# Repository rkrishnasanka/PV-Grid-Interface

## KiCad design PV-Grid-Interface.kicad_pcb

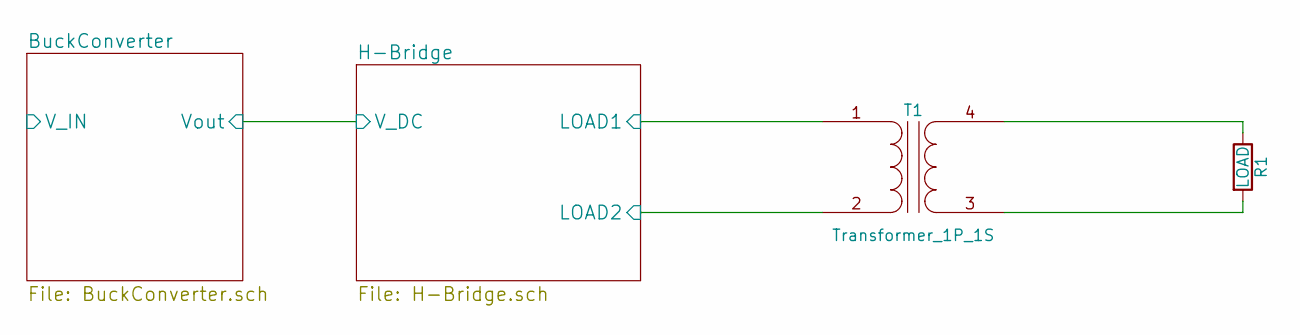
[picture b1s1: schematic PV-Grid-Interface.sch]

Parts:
R1: LOAD
T1: Transformer_1P_1S

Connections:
unnamed: R1.1, T1.4 (SB)
unnamed: R1.2, T1.3 (SA)

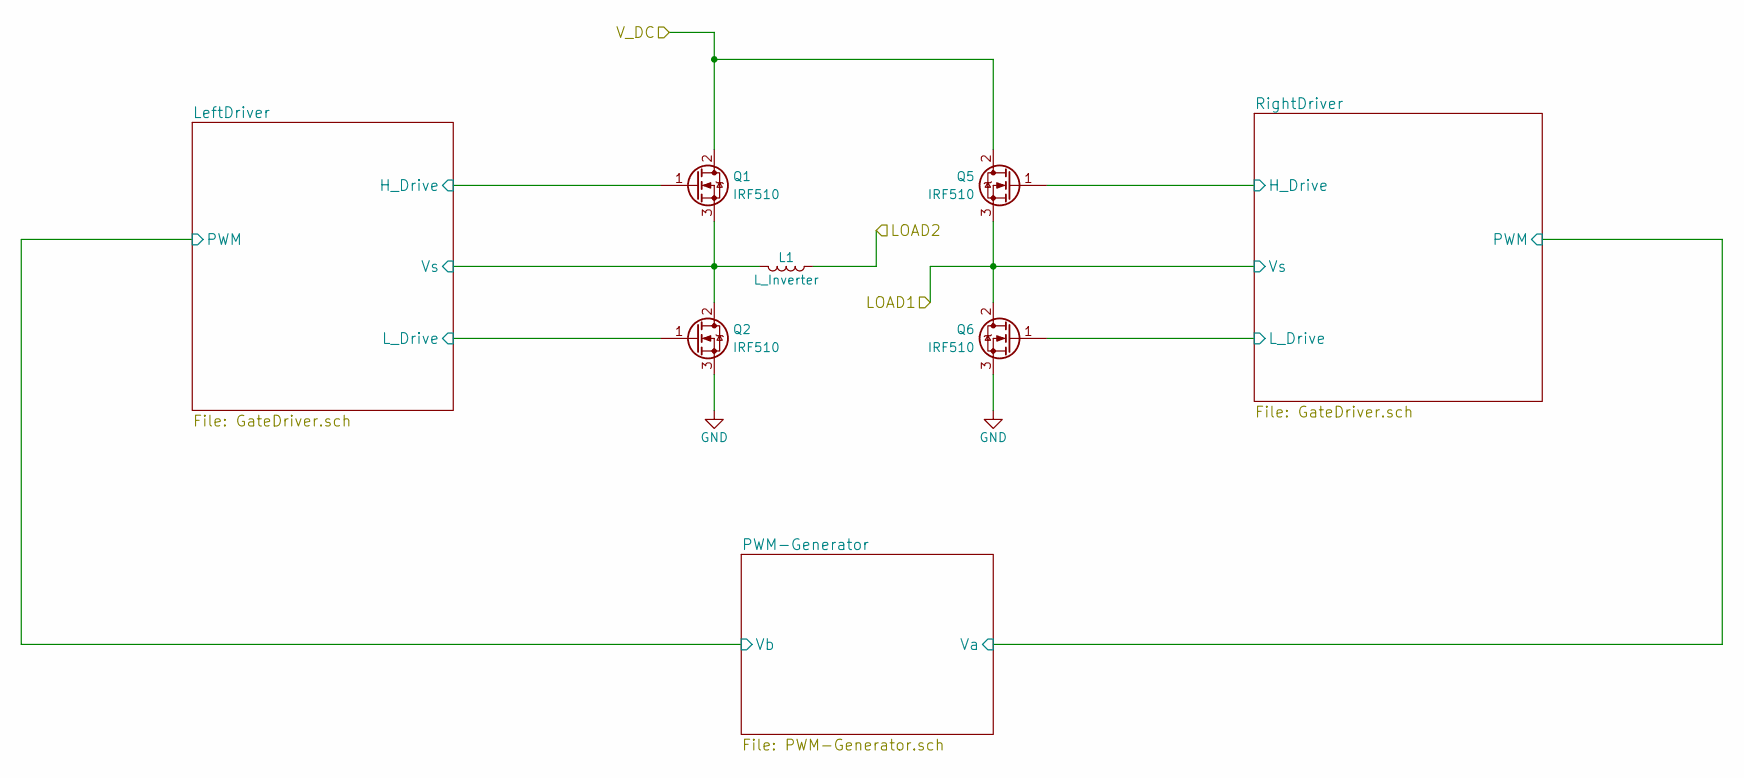
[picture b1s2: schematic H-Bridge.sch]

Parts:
L1: L_Inverter
Q1, Q2, Q5, Q6: IRF510; TO-220_Neutral123_Vertical

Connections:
/H-Bridge/LOAD1: Q5.3 (S), Q6.2 (D); also elsewhere on the board
/H-Bridge/LeftDriver/H_Drive: Q1.1 (G); also elsewhere on the board
/H-Bridge/LeftDriver/L_Drive: Q2.1 (G); also elsewhere on the board
/H-Bridge/LeftDriver/Vs: L1.2, Q1.3 (S), Q2.2 (D); also elsewhere on the board
/H-Bridge/RightDriver/H_Drive: Q5.1 (G); also elsewhere on the board
/H-Bridge/RightDriver/L_Drive: Q6.1 (G); also elsewhere on the board
/H-Bridge/V_DC: Q1.2 (D), Q5.2 (D); also elsewhere on the board
GND: Q2.3 (S), Q6.3 (S); also elsewhere on the board

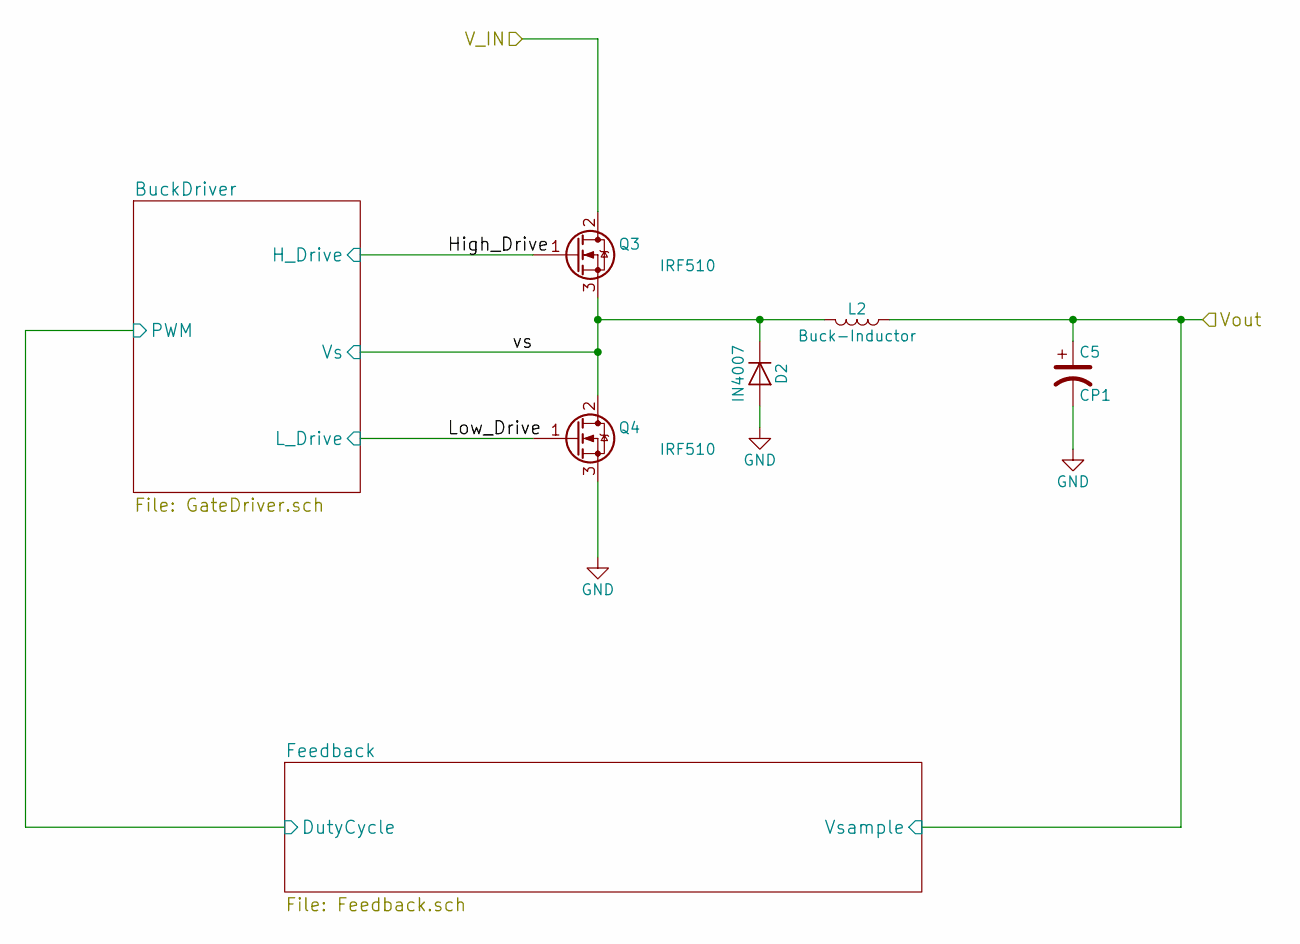
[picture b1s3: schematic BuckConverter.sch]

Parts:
C5: CP1; C_Radial_D16_L30_P7.5
D2: IN4007; Diode_DO-35_SOD27_Horizontal_RM10
L2: Buck-Inductor
Q3, Q4: IRF510; TO-220_Neutral123_Vertical

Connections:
/BuckConverter/High_Drive: Q3.1 (G); also elsewhere on the board
/BuckConverter/Low_Drive: Q4.1 (G); also elsewhere on the board
/BuckConverter/V_IN: Q3.2 (D)
/BuckConverter/vs: D2.1 (K), L2.2, Q3.3 (S), Q4.2 (D); also elsewhere on the board
/H-Bridge/V_DC: C5.1, L2.1; also elsewhere on the board
GND: C5.2, D2.2 (A), Q4.3 (S); also elsewhere on the board

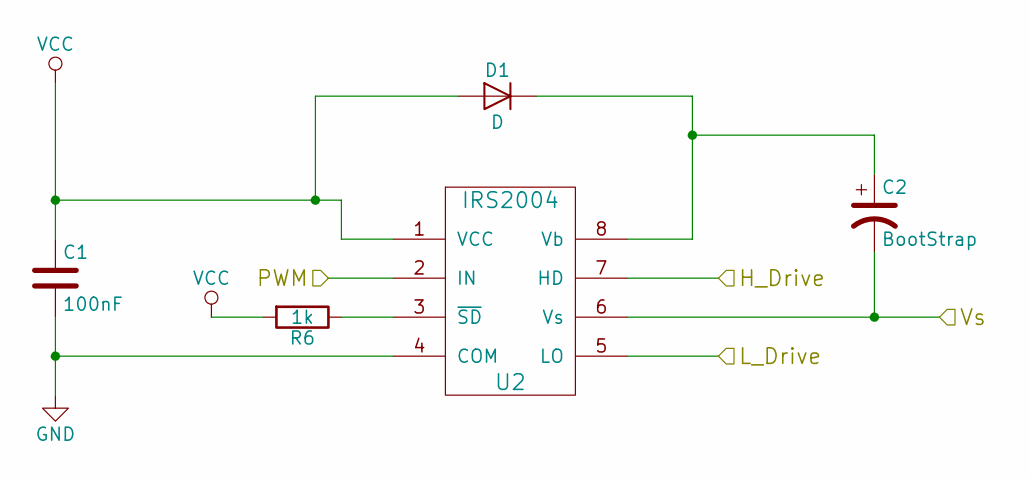
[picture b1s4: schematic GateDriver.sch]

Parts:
C2: BootStrap; C_Disc_D3_P2.5
C3: 100nF; C_Disc_D3_P2.5
D1: D; Diode_DO-35_SOD27_Horizontal_RM10
R6: 1k; Resistor_Horizontal_RM7mm
U2: IRS2004; DIP-8_W7.62mm_LongPads

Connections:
/H-Bridge/LeftDriver/H_Drive: U2.7 (HD); also elsewhere on the board
/H-Bridge/LeftDriver/L_Drive: U2.5 (LO); also elsewhere on the board
/H-Bridge/LeftDriver/PWM: U2.2 (IN); also elsewhere on the board
/H-Bridge/LeftDriver/Vs: C2.2, U2.6 (Vs); also elsewhere on the board
GND: C3.2, U2.4 (COM); also elsewhere on the board
unnamed: C2.1, D1.1 (K), U2.8 (Vb)
unnamed: R6.1, U2.3 (~SD)
VCC: C3.1, D1.2 (A), R6.2, U2.1 (VCC); also elsewhere on the board

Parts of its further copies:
C1, C10: 100nF; C_Disc_D3_P2.5
C4, C11: BootStrap; C_Disc_D3_P2.5
D3, D4: D; Diode_DO-35_SOD27_Horizontal_RM10
R7, R16: 1k; Resistor_Horizontal_RM7mm
U4, U12: IRS2004; DIP-8_W7.62mm_LongPads

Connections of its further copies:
/BuckConverter/Feedback/DutyCycle: U12.2 (IN); also elsewhere on the board
/BuckConverter/High_Drive: U12.7 (HD); also elsewhere on the board
/BuckConverter/Low_Drive: U12.5 (LO); also elsewhere on the board
/BuckConverter/vs: C11.2, U12.6 (Vs); also elsewhere on the board
/H-Bridge/LOAD1: C4.2, U4.6 (Vs); also elsewhere on the board
/H-Bridge/RightDriver/H_Drive: U4.7 (HD); also elsewhere on the board
/H-Bridge/RightDriver/L_Drive: U4.5 (LO); also elsewhere on the board
/H-Bridge/RightDriver/PWM: U4.2 (IN); also elsewhere on the board
GND: C1.2, C10.2, U4.4 (COM), U12.4 (COM); also elsewhere on the board
unnamed: C4.1, D3.1 (K), U4.8 (Vb)
unnamed: C11.1, D4.1 (K), U12.8 (Vb)
unnamed: R7.1, U4.3 (~SD)
unnamed: R16.1, U12.3 (~SD)
VCC: C1.1, C10.1, D3.2 (A), D4.2 (A), R7.2, R16.2, U4.1 (VCC), U12.1 (VCC); also elsewhere on the board

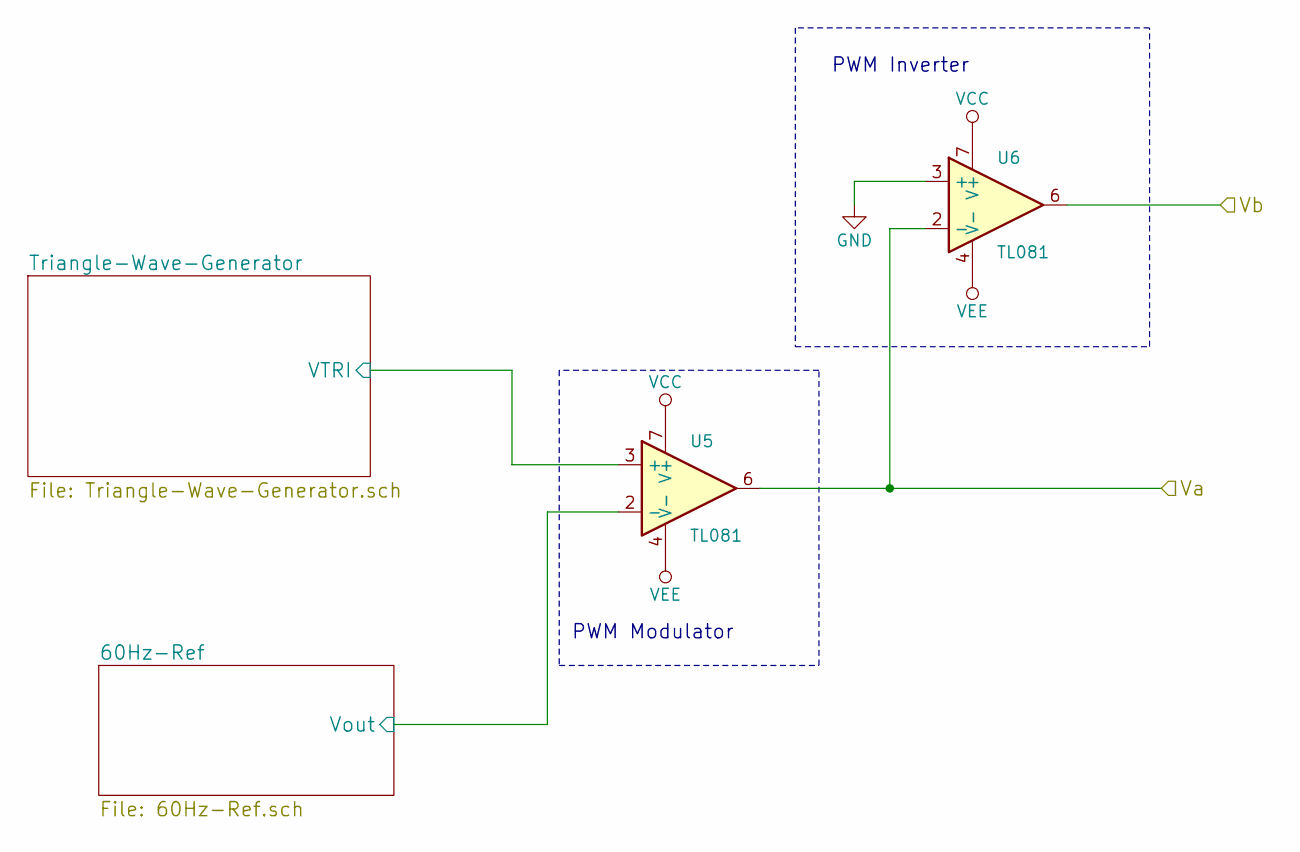
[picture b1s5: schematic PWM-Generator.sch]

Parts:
U5, U6: TL081; DIP-8_W7.62mm_LongPads

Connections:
/H-Bridge/LeftDriver/PWM: U6.6; also elsewhere on the board
/H-Bridge/PWM-Generator/60Hz-Ref/Vout: U5.2 (-); also elsewhere on the board
/H-Bridge/PWM-Generator/Triangle-Wave-Generator/VTRI: U5.3 (+); also elsewhere on the board
/H-Bridge/RightDriver/PWM: U5.6, U6.2 (-); also elsewhere on the board
GND: U6.3 (+); also elsewhere on the board
VCC: U5.7 (V+), U6.7 (V+); also elsewhere on the board
VEE: U5.4 (V-), U6.4 (V-); also elsewhere on the board

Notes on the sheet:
PWM Modulator
PWM Inverter

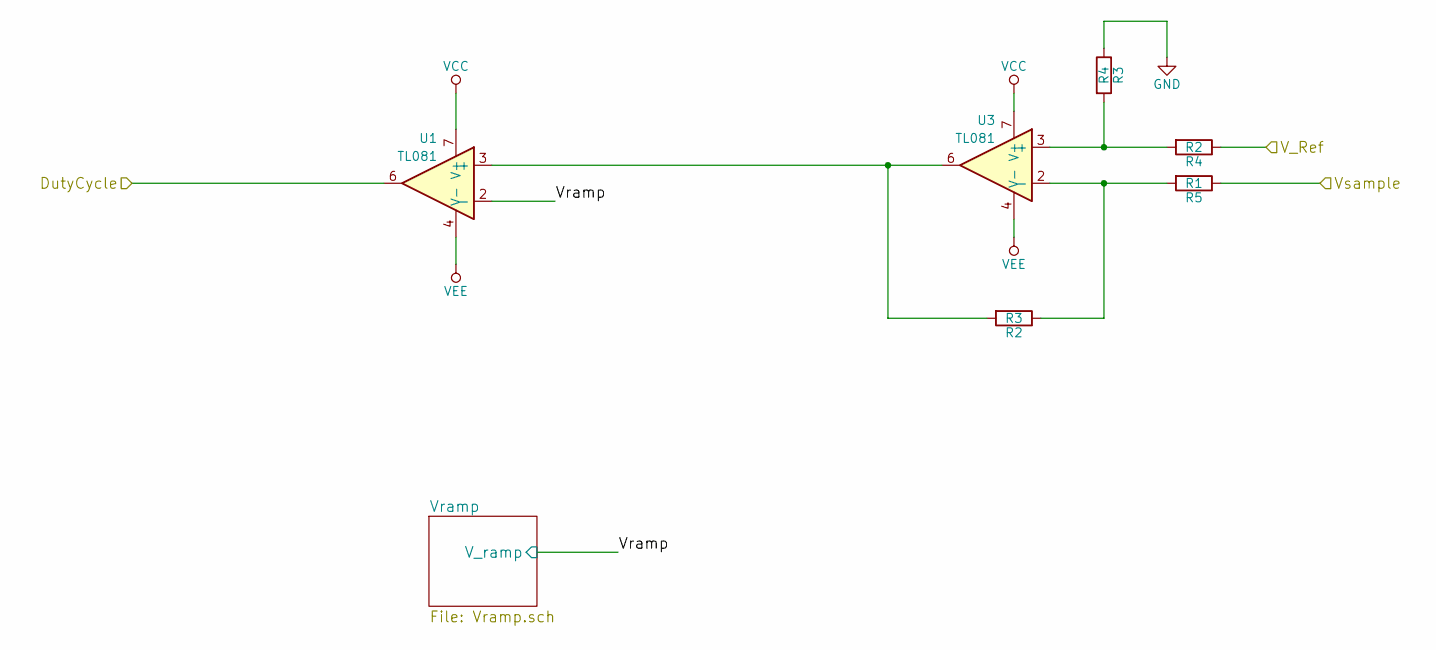
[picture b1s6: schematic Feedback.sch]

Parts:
R2: R3; Resistor_Horizontal_RM7mm
R3: R4; Resistor_Horizontal_RM7mm
R4: R2; Resistor_Horizontal_RM7mm
R5: R1; Resistor_Horizontal_RM7mm
U1, U3: TL081; DIP-8_W7.62mm_LongPads

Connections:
/BuckConverter/Feedback/DutyCycle: U1.6; also elsewhere on the board
/BuckConverter/Feedback/V_Ref: R4.1
/BuckConverter/Feedback/Vramp: U1.2 (-); also elsewhere on the board
/H-Bridge/V_DC: R5.1; also elsewhere on the board
GND: R3.1; also elsewhere on the board
unnamed: R2.1, R5.2, U3.2 (-)
unnamed: R2.2, U1.3 (+), U3.6
unnamed: R3.2, R4.2, U3.3 (+)
VCC: U1.7 (V+), U3.7 (V+); also elsewhere on the board
VEE: U1.4 (V-), U3.4 (V-); also elsewhere on the board

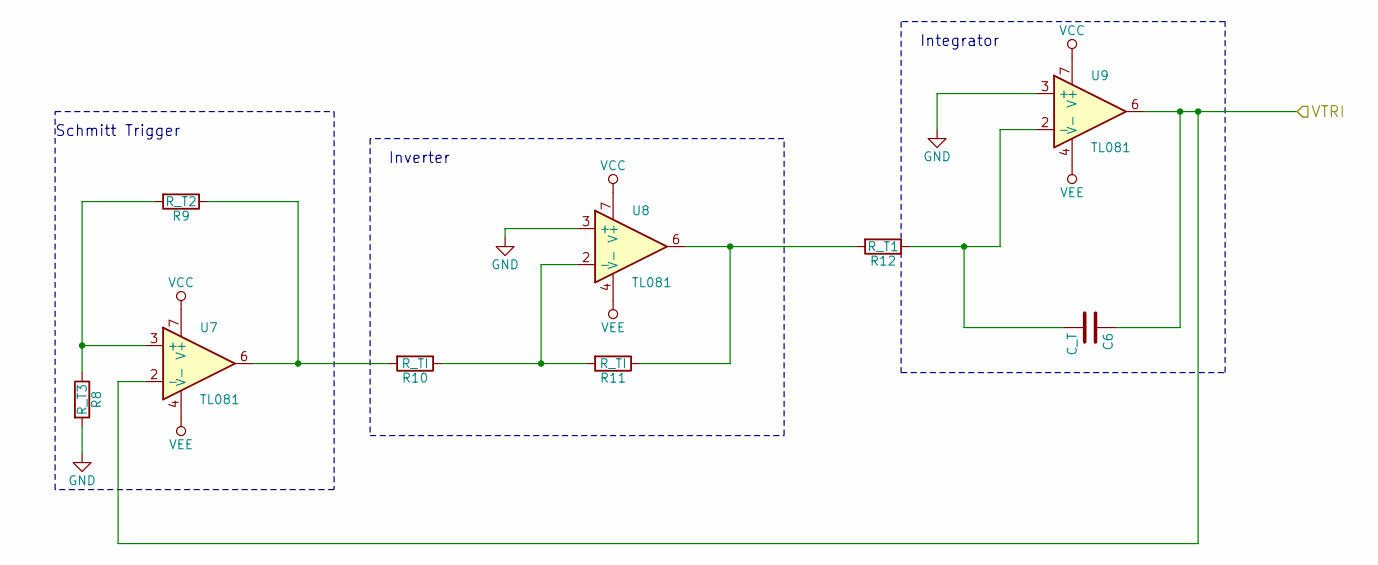
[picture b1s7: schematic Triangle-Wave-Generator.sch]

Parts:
C6: C_T; C_Disc_D3_P2.5
R8: R_T3; Resistor_Horizontal_RM7mm
R9: R_T2; Resistor_Horizontal_RM7mm
R10, R11: R_TI; Resistor_Horizontal_RM7mm
R12: R_T1; Resistor_Horizontal_RM7mm
U7, U8, U9: TL081; DIP-8_W7.62mm_LongPads

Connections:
/H-Bridge/PWM-Generator/Triangle-Wave-Generator/VTRI: C6.1, U7.2 (-), U9.6; also elsewhere on the board
GND: R8.2, U8.3 (+), U9.3 (+); also elsewhere on the board
unnamed: C6.2, R12.1, U9.2 (-)
unnamed: R8.1, R9.2, U7.3 (+)
unnamed: R10.1, R11.2, U8.2 (-)
unnamed: R9.1, R10.2, U7.6
unnamed: R11.1, R12.2, U8.6
VCC: U7.7 (V+), U8.7 (V+), U9.7 (V+); also elsewhere on the board
VEE: U7.4 (V-), U8.4 (V-), U9.4 (V-); also elsewhere on the board

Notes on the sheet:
Schmitt Trigger
Integrator
Inverter

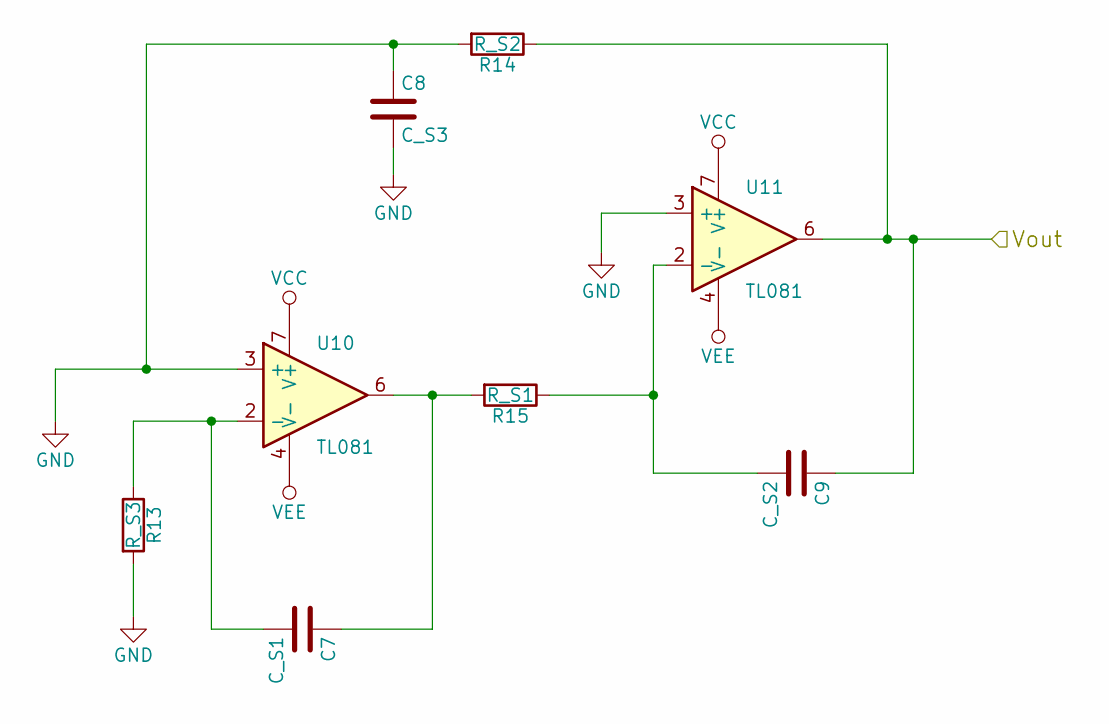
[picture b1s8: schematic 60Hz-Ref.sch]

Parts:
C7: C_S1; C_Disc_D3_P2.5
C8: C_S3; C_Disc_D3_P2.5
C9: C_S2; C_Disc_D3_P2.5
R13: R_S3; Resistor_Horizontal_RM7mm
R14: R_S2; Resistor_Horizontal_RM7mm
R15: R_S1; Resistor_Horizontal_RM7mm
U10, U11: TL081; DIP-8_W7.62mm_LongPads

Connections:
/H-Bridge/PWM-Generator/60Hz-Ref/Vout: C9.1, R14.1, U11.6; also elsewhere on the board
GND: C8.1, C8.2, R13.2, R14.2, U10.3 (+), U11.3 (+); also elsewhere on the board
unnamed: C7.1, R15.2, U10.6
unnamed: C7.2, R13.1, U10.2 (-)
unnamed: C9.2, R15.1, U11.2 (-)
VCC: U10.7 (V+), U11.7 (V+); also elsewhere on the board
VEE: U10.4 (V-), U11.4 (V-); also elsewhere on the board

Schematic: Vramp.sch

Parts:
C12, C13: 0.01uF; C_Disc_D3_P2.5
Q7, Q8: 2N2907; TO-92_Inline_Wide
Q9: 2N2222; TO-92_Inline_Wide
R17, R20: 1k; Resistor_Horizontal_RM7mm
R18, R19, R21: 10k; Resistor_Horizontal_RM7mm

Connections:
/BuckConverter/Feedback/Vramp: C12.1, C13.1, Q7.3 (C), Q8.1 (E); also elsewhere on the board
GND: C12.2, C13.2, Q9.1 (E), R18.2, R21.2; also elsewhere on the board
unnamed: Q7.1 (E), R19.2
unnamed: Q7.2 (B), R17.2, R18.1
unnamed: Q8.2 (B), Q9.3 (C), R20.2, R21.1
unnamed: Q8.3 (C), Q9.2 (B)
VCC: R17.1, R19.1, R20.1; also elsewhere on the board

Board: 2 copper layers, 58 parts (0 on the bottom side), 40 nets, no tracks yet.

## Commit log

2017-05-09 Initial Commit - Has all the schematics
    TODO:
    Need to add data sheets and reference information
